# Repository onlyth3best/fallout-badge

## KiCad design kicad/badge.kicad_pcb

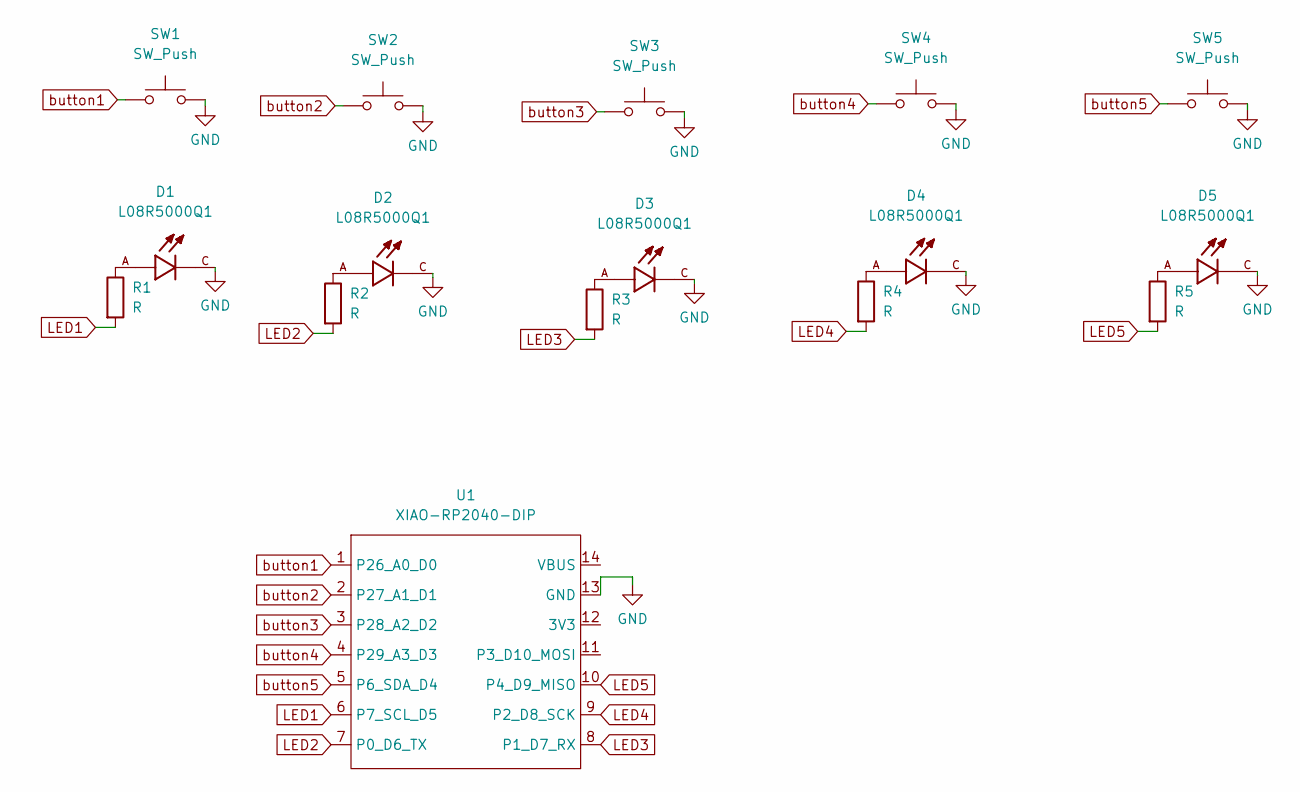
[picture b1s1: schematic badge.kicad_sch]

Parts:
D1, D2, D3, D4, D5: L08R5000Q1; LEDRD254W57D500H1070; PARTREV NA
R1, R2, R3, R4, R5: R; R_Axial_DIN0204_L3.6mm_D1.6mm_P5.08mm_Horizontal
SW1, SW2, SW3, SW4, SW5: SW_Push; SW_PUSH_6mm
U1: XIAO-RP2040-DIP

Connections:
GND: D1.C, D2.C, D3.C, D4.C, D5.C, SW1.2, SW2.2, SW3.2, SW4.2, SW5.2, U1.13 (GND)
LED1: R1.2, U1.6 (P7_SCL_D5)
LED2: R2.2, U1.7 (P0_D6_TX)
LED3: R3.2, U1.8 (P1_D7_RX)
LED4: R4.2, U1.9 (P2_D8_SCK)
LED5: R5.2, U1.10 (P4_D9_MISO)
unnamed: D1.A, R1.1
unnamed: D2.A, R2.1
unnamed: D3.A, R3.1
unnamed: D4.A, R4.1
unnamed: D5.A, R5.1
button1: SW1.1, U1.1 (P26_A0_D0)
button2: SW2.1, U1.2 (P27_A1_D1)
button3: SW3.1, U1.3 (P28_A2_D2)
button4: SW4.1, U1.4 (P29_A3_D3)
button5: SW5.1, U1.5 (P6_SDA_D4)

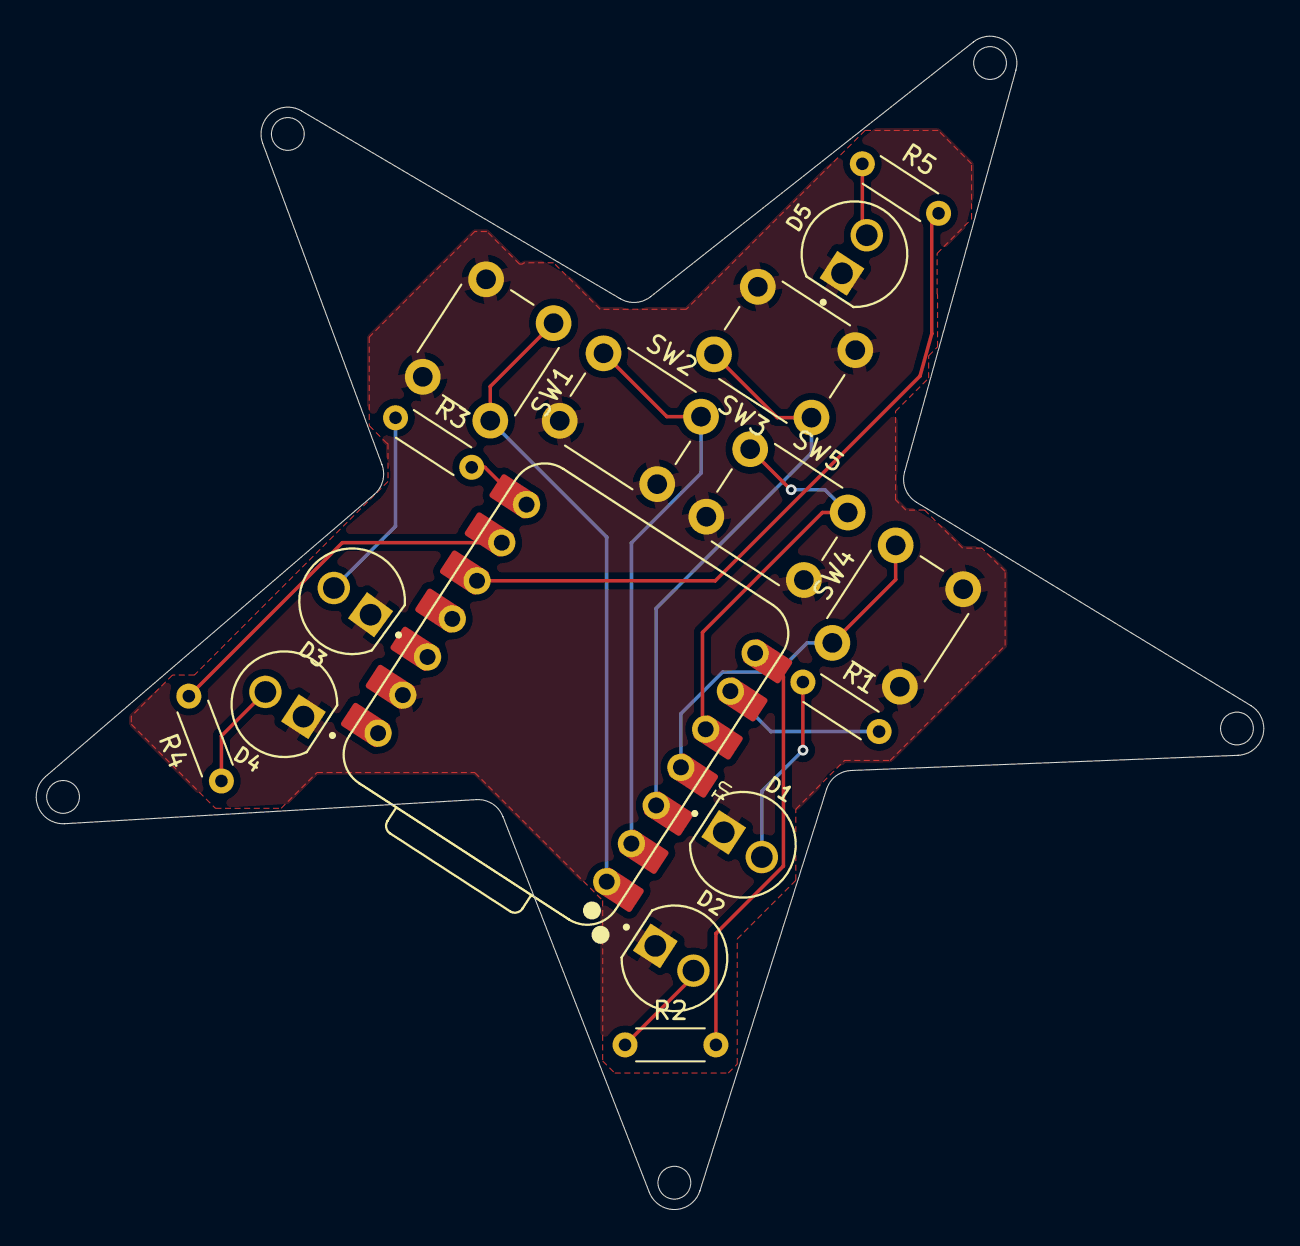
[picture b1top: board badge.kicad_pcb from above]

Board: 2 copper layers, 68.6 x 65.6 mm, 16 parts (0 on the bottom side), 16 nets.

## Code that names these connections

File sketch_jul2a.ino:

int BUT1 = D0;
int BUT2 = D1;
int BUT3 = D2;
int BUT4 = D3;
int BUT5 = D4;
int LED1 = D5;
int LED2 = D6;
int LED3 = D7;
int LED4 = D8;
int LED5 = D9;

bool L1 = false;
bool L2 = false;
bool L3 = false;
bool L4 = false;
bool L5 = false;
bool L6 = false;

void setup() {
  // put your setup code here, to run once:
  pinMode(BUT1, INPUT_PULLUP);
  pinMode(BUT2, INPUT_PULLUP);
  pinMode(BUT3, INPUT_PULLUP);
  pinMode(BUT4, INPUT_PULLUP);
  pinMode(BUT5, INPUT_PULLUP);

  pinMode(LED1, OUTPUT);
  pinMode(LED2, OUTPUT);
  pinMode(LED3, OUTPUT);
  pinMode(LED4, OUTPUT);
  pinMode(LED5, OUTPUT);

}

void loop() {
  // put your main code here, to run repeatedly:
  //update the LEDs acc. 2 bools
  digitalWrite(LED1, L1);
  digitalWrite(LED2, L2);
  digitalWrite(LED3, L3);
  digitalWrite(LED4, L4);
  digitalWrite(LED5, L5);

  //button fucntionaliyt
  if (digitalRead(BUT1) == HIGH) {
    L1 = !L1;
    L2 = !L2;
    L3 = !L3;
    delay(100);
}

  if (digitalRead(BUT2) == HIGH) {
    L1 = !L1;
    L4 = !L4;
    L5 = !L5;
    delay(100);
}

  if (digitalRead(BUT3) == HIGH) {
    L1 = !L1;
    L2 = !L2;
    L4 = !L4;
    delay(100);
}

  if (digitalRead(BUT4) == HIGH) {
    L3 = !L3;
    L4 = !L4;
    L5 = !L5;
    delay(100);
}

  if (digitalRead(BUT5) == HIGH) {
    L2 = !L2;
    L3 = !L3;
    L5 = !L5;
    delay(100);
}


// iff all are on:
  if (L1 && L2 && L3 && L4 && L5) {
    digitalWrite(LED1, HIGH);
    delay(200);
    digitalWrite(LED2, HIGH);
    delay(200);
    digitalWrite(LED3, HIGH);
    delay(200);
    digitalWrite(LED4, HIGH);
    delay(200);
    digitalWrite(LED5, HIGH);
    delay(200);

    digitalWrite(LED1, LOW);
   digitalWrite(led_Pin_2, LOW);
    delay(300);
    digitalWrite(LED2, LOW);
    delay(300);
    digitalWrite(LED3, LOW);
    delay(300);
    digitalWrite(LED4, LOW);
    delay(300);
    digitalWrite(LED5, HIGH);
    delay(300);
  }

// main NEMAZAT
}
